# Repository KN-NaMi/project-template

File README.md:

# Project Template

Multi-disciplinary project template for electronics, mechanics, and software development.

## 📁 Structure

```
project-template/
├── README.md                 # Project overview
├── bom.csv                   # Bill of Materials
├── electronics/              # Electronics
├── mechanics/                # Mechanical
└── software/                 # Software
```

## 🚀 Quick Start

1. Clone this template for your new project
2. Customize folder names and content
3. Add your design files and code
4. Update README files with project details

## 📋 Features

- **Electronics** - PCB design, simulations
- **Mechanics** - CAD files, drawings, 3D printing
- **Software** - Apps, firmware, scripts

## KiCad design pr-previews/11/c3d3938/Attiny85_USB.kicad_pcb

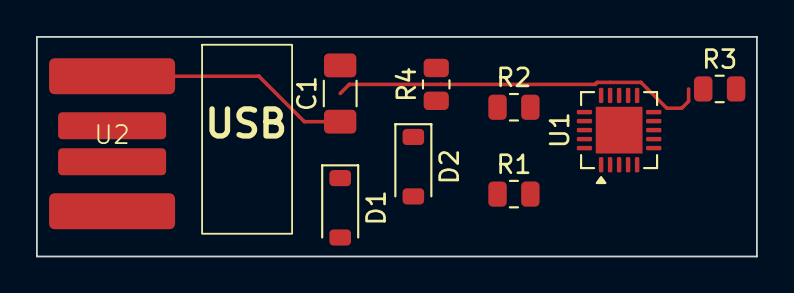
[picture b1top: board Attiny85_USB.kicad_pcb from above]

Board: 2 copper layers, 40.0 x 12.2 mm, 9 parts (0 on the bottom side), 7 nets.

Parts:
C1: 100n; C_1206_3216Metric_Pad1.33x1.80mm_HandSolder
D1, D2: 3V6; D_SOD-123
R1, R2: 68R; R_0805_2012Metric
R3: 330R; R_0805_2012Metric
R4: 1k5; R_0805_2012Metric
U1: ATtiny85-20M; QFN-20-1EP_4x4mm_P0.5mm_EP2.6x2.6mm
U2: custom_footp

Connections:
+5V: C1.1, R4.1, U1.15 (VCC), U2.1 (Vcc)
GND: C1.2, D2.2 (A), U1.8 (GND), U1.21 (GND), U2.4 (GND)
unnamed: D1.1 (K), R2.2, R4.2, U2.2 (D+)
unnamed: D2.1 (K), R1.2, U2.3 (D-)
unnamed: R3.1, U1.12 (PB1)
unnamed: R1.1, U1.5 (XTAL2/PB4)
unnamed: R2.1, U1.2 (XTAL1/PB3)

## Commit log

2025-08-15 project template v1
2025-08-15 Update LICENSE file for improved formatting
2025-11-11 Update Kiri output for PR #7
2025-11-11 Update Kiri output for PR #9
2025-11-11 Update Kiri output for PR #11
2025-11-15 Update README files for electronics project structure and add 3D models documentation
2025-11-16 Refactor README files for project structure and add Gerber files documentation
2025-11-16 test diode
2025-11-16 Refactor KiCad PR workflow to improve project discovery and output handling
2025-11-16 Refactor project file collection in KiCad PR workflow to improve JSON formatting
2025-11-16 Add environment variables for Kiri action in KiCad PR workflow
2025-11-16 Refactor Kiri execution in KiCad PR workflow to use Docker and improve output handling
2025-11-16 Refactor Kiri execution in KiCad PR workflow to improve JSON handling and update volume mount path
2025-11-16 Refactor GitHub Actions workflow for KiCad PR Diff: streamline project discovery and Kiri execution steps
2025-11-16 Add initial KiCad PCB, PRL, PRO, and SCH files for board1 with complete configurations and components
2025-11-16 Enhance Kiri execution step in GitHub Actions: add entrypoint override for Docker run command
2025-11-16 Refactor GitHub Actions workflow for KiCad PR Diff: improve project discovery and update Kiri execution steps
2025-11-16 kiri test
2025-11-16 fix kiri workflow
2025-11-16 Refactor Kiri-Docker step in GitHub Actions workflow: improve echo statements formatting
2025-11-16 Refactor Kiri-Docker
2025-11-16 tests
2025-11-16 test
2025-11-16 install kiri
